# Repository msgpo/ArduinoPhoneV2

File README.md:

# ArduinoPhoneV2
Arduino Phone V2.0

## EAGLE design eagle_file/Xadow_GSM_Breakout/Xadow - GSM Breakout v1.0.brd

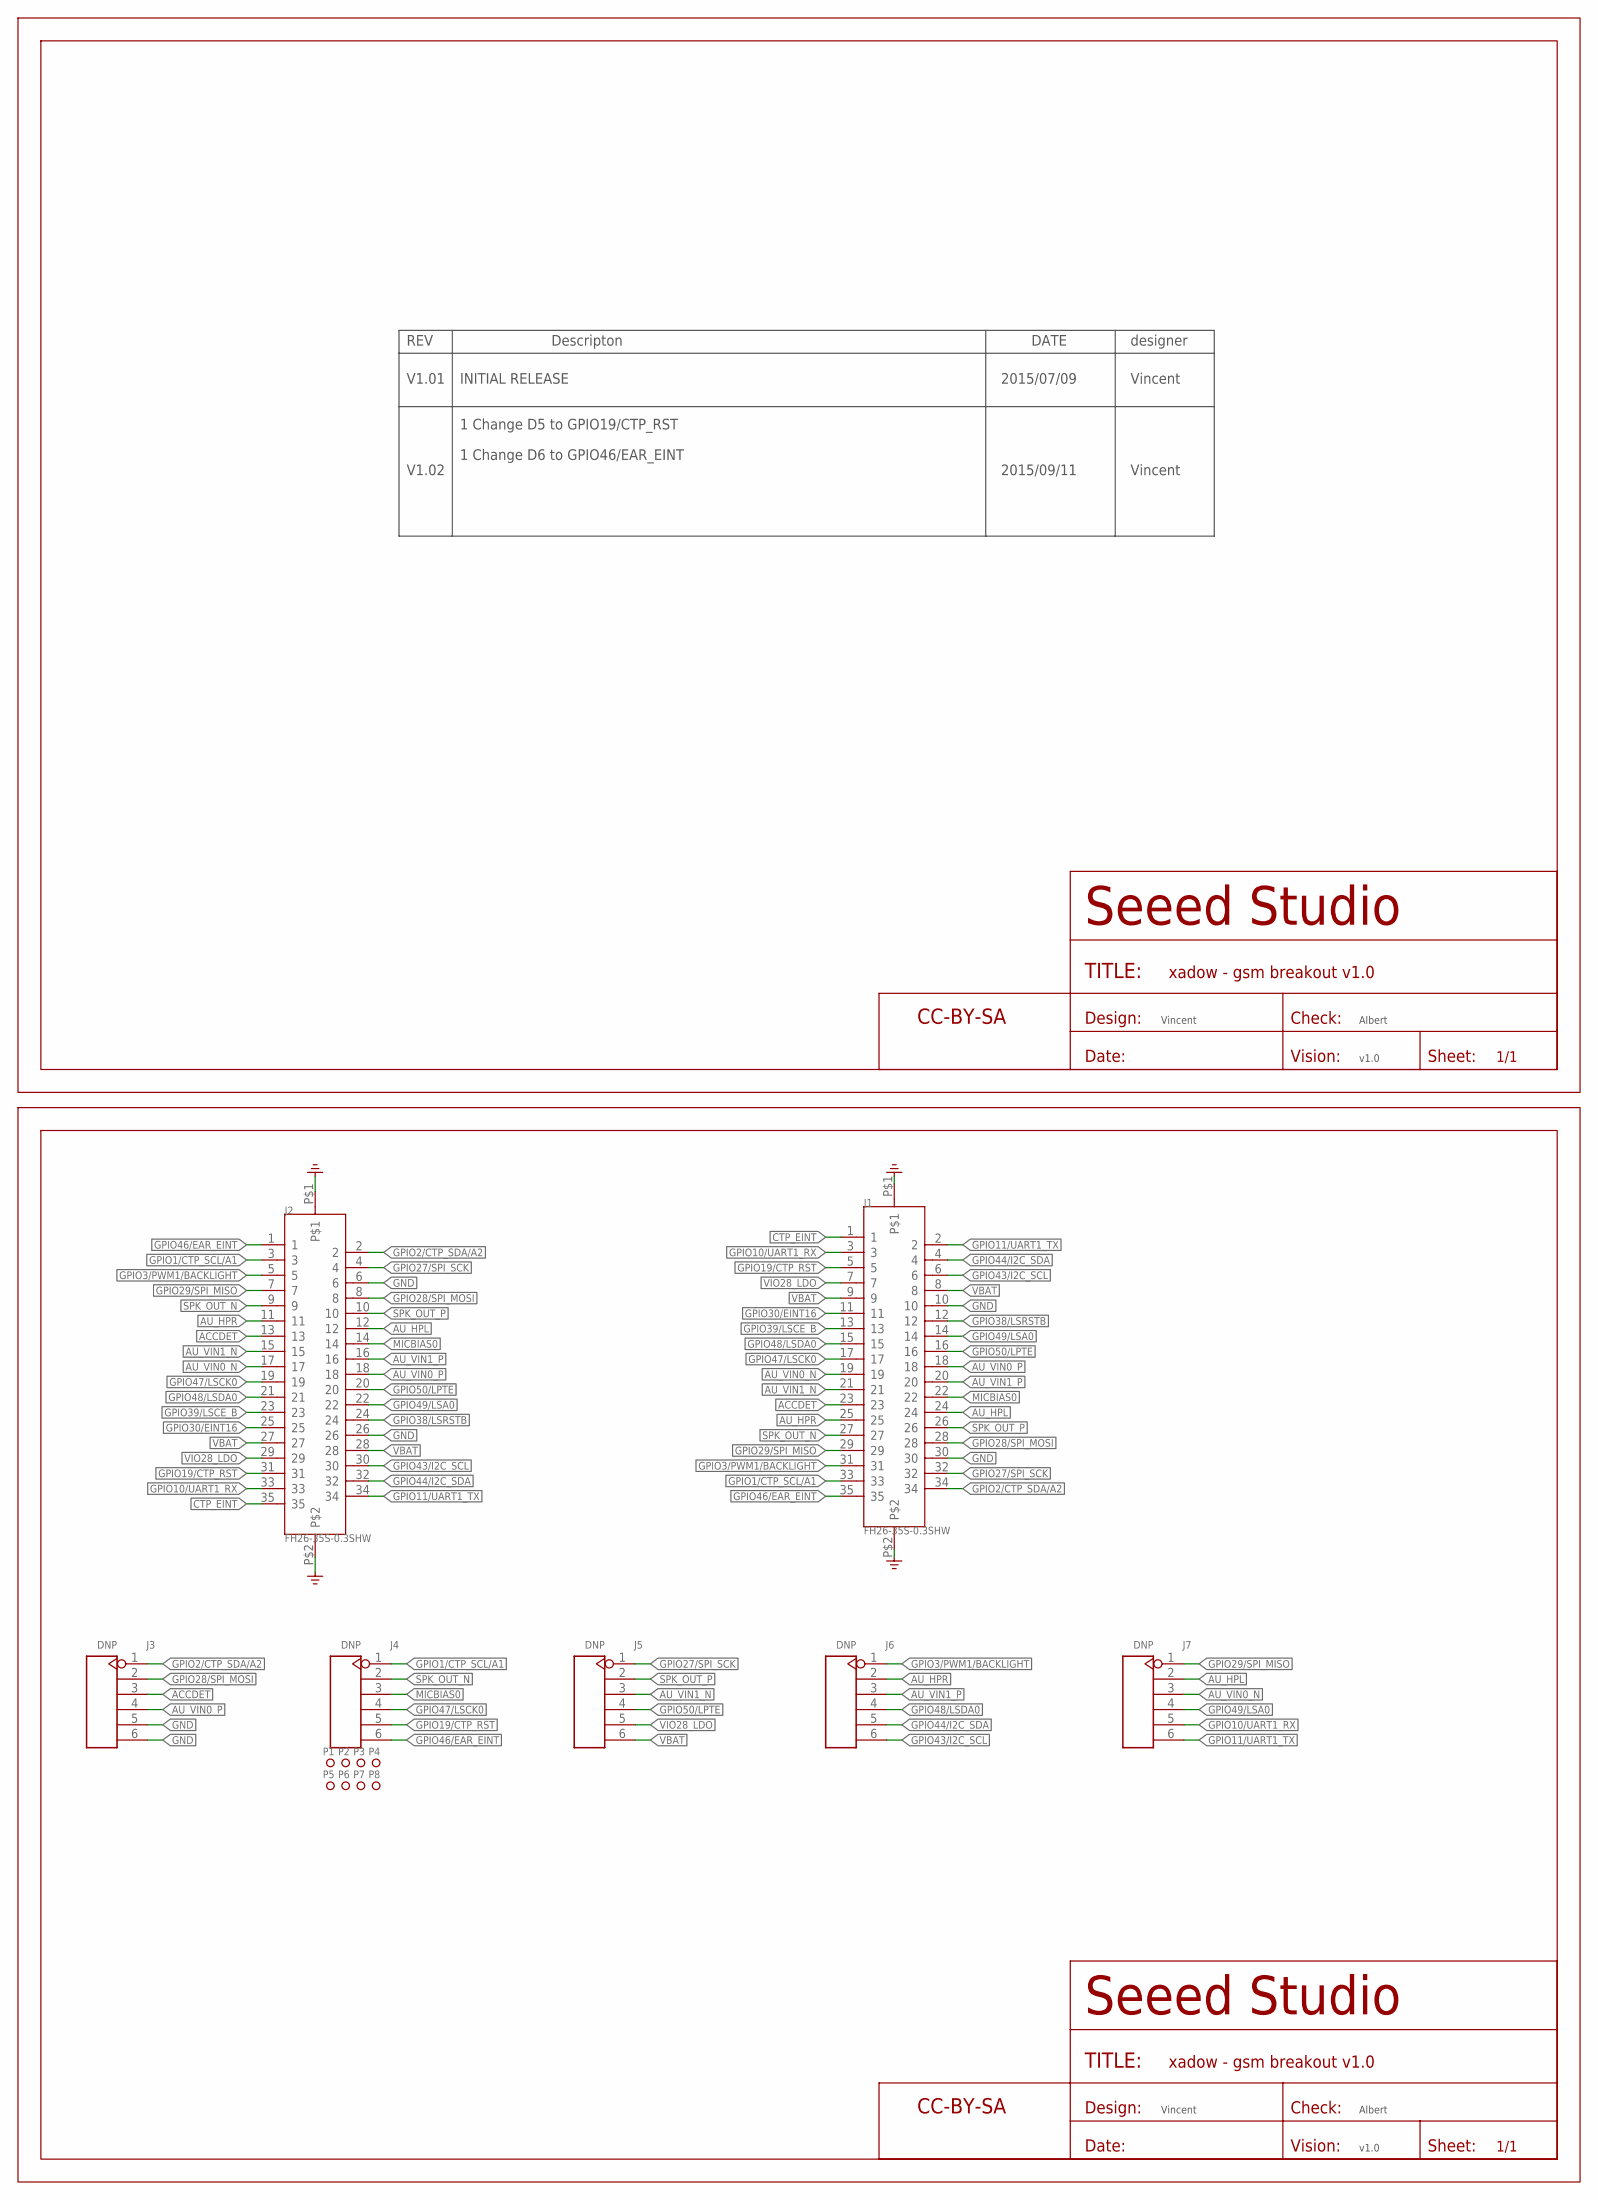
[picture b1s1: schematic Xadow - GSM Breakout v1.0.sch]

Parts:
FR1, FR2: SEEEDSTUDIO-OPEN-SCH-FRAME; SEEEDSTUDIO-PCB-FRAME
J1, J2: FH26-35S-0.3SHW; FPC35-SMD-0.3(FH26W)
J3, J4, J5, J6, J7: DNP; H6-2.54-C65D35MIL
P1, P2, P3, P4, P5, P6, P7, P8: MARK-1.0'ANNULAR'; ROUND-MARK-1.0

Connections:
ACCDET: J1.23, J2.13, J3.3
AU_HPL: J1.24, J2.12, J7.2
AU_HPR: J1.25, J2.11, J6.2
AU_VIN0_N: J1.19, J2.17, J7.3
AU_VIN0_P: J1.18, J2.18, J3.4
AU_VIN1_N: J1.21, J2.15, J5.3
AU_VIN1_P: J1.20, J2.16, J6.3
CTP_EINT: J1.1, J2.35
GND: J1.10, J1.30, J1.P$1, J1.P$2, J2.6, J2.26, J2.P$1, J2.P$2, J3.5, J3.6
GPIO1/CTP_SCL/A1: J1.33, J2.3, J4.1
GPIO2/CTP_SDA/A2: J1.34, J2.2, J3.1
GPIO3/PWM1/BACKLIGHT: J1.31, J2.5, J6.1
GPIO10/UART1_RX: J1.3, J2.33, J7.5
GPIO11/UART1_TX: J1.2, J2.34, J7.6
GPIO19/CTP_RST: J1.5, J2.31, J4.5
GPIO27/SPI_SCK: J1.32, J2.4, J5.1
GPIO28/SPI_MOSI: J1.28, J2.8, J3.2
GPIO29/SPI_MISO: J1.29, J2.7, J7.1
GPIO30/EINT16: J1.11, J2.25
GPIO38/LSRSTB: J1.12, J2.24
GPIO39/LSCE_B: J1.13, J2.23
GPIO43/I2C_SCL: J1.6, J2.30, J6.6
GPIO44/I2C_SDA: J1.4, J2.32, J6.5
GPIO46/EAR_EINT: J1.35, J2.1, J4.6
GPIO47/LSCK0: J1.17, J2.19, J4.4
GPIO48/LSDA0: J1.15, J2.21, J6.4
GPIO49/LSA0: J1.14, J2.22, J7.4
GPIO50/LPTE: J1.16, J2.20, J5.4
MICBIAS0: J1.22, J2.14, J4.3
SPK_OUT_N: J1.27, J2.9, J4.2
SPK_OUT_P: J1.26, J2.10, J5.2
VBAT: J1.8, J1.9, J2.27, J2.28, J5.6
VIO28_LDO: J1.7, J2.29, J5.5

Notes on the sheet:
REV
Descripton
DATE
designer
V1.01
INITIAL RELEASE
V1.02
1 Change D5 to GPIO19/CTP_RST
2015/07/09
2015/09/11
Vincent
1 Change D6 to GPIO46/EAR_EINT
Albert
v1.0

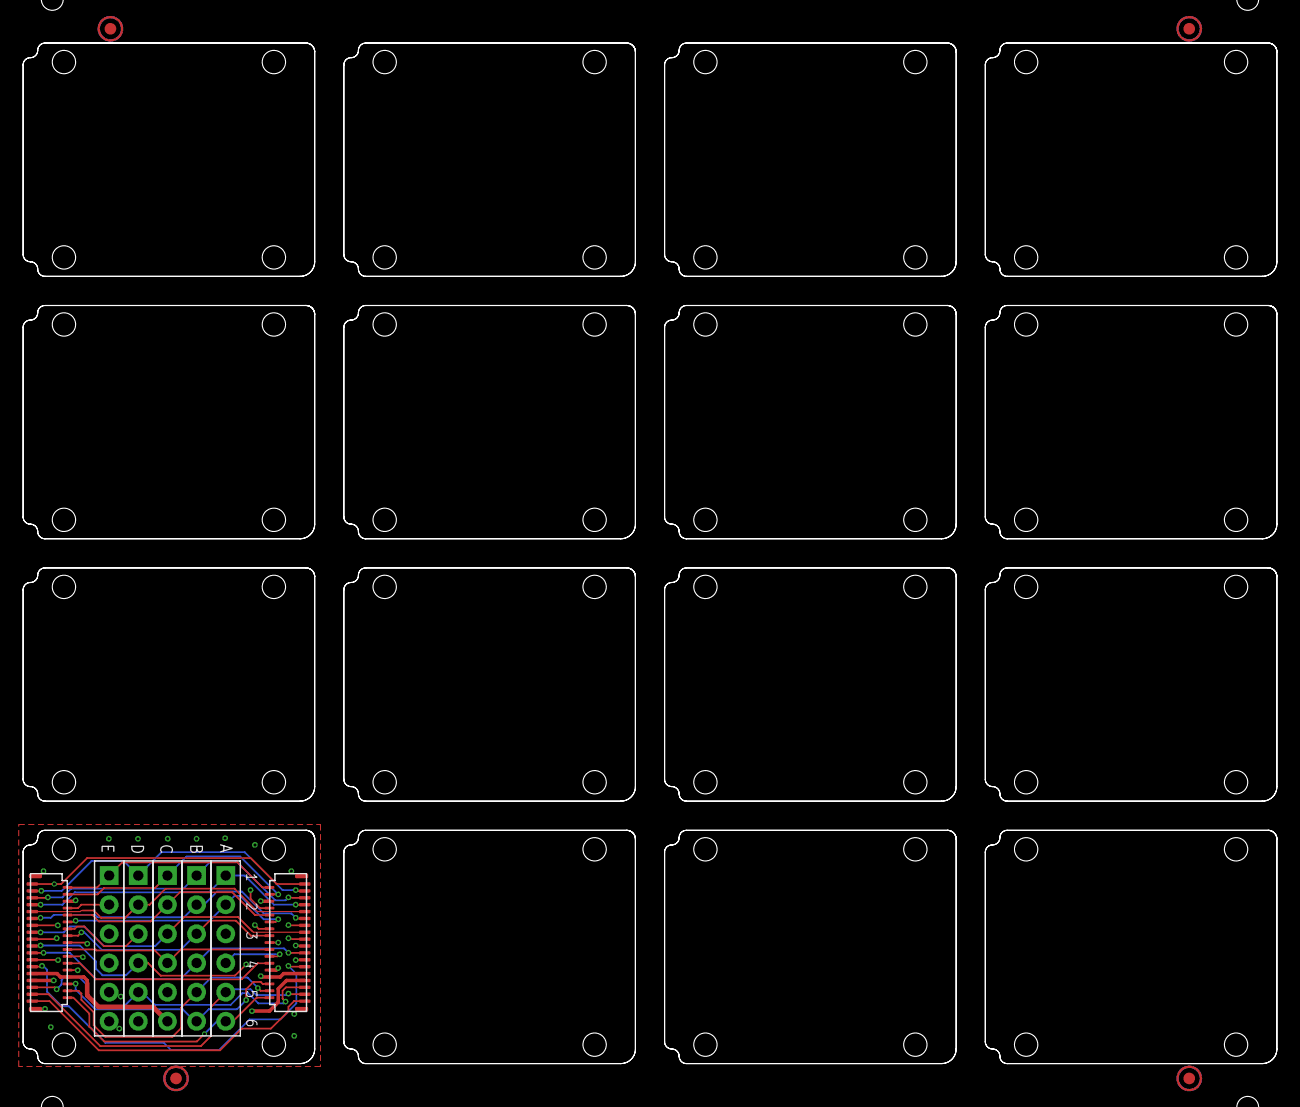
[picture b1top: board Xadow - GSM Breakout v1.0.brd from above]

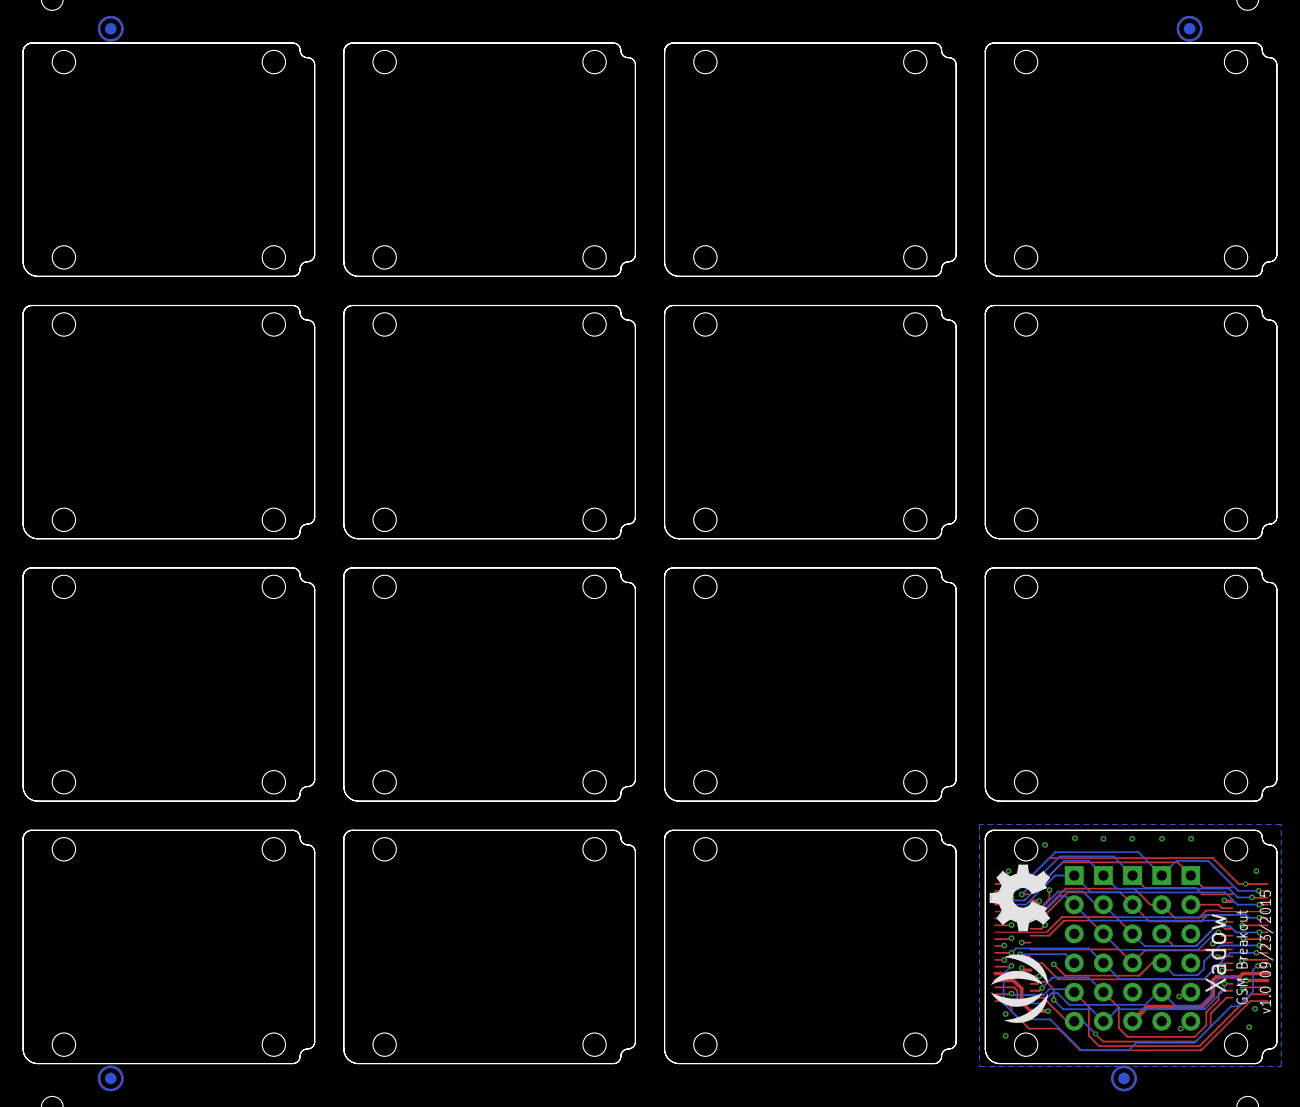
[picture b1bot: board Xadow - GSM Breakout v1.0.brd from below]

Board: 4 copper layers, 109.2 x 88.9 mm, 19 parts (6 on the bottom side), 33 nets.

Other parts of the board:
U$18: OSHW_FILLX200_NOTEXT
U$20: SEEED-SILK-280*268MIL

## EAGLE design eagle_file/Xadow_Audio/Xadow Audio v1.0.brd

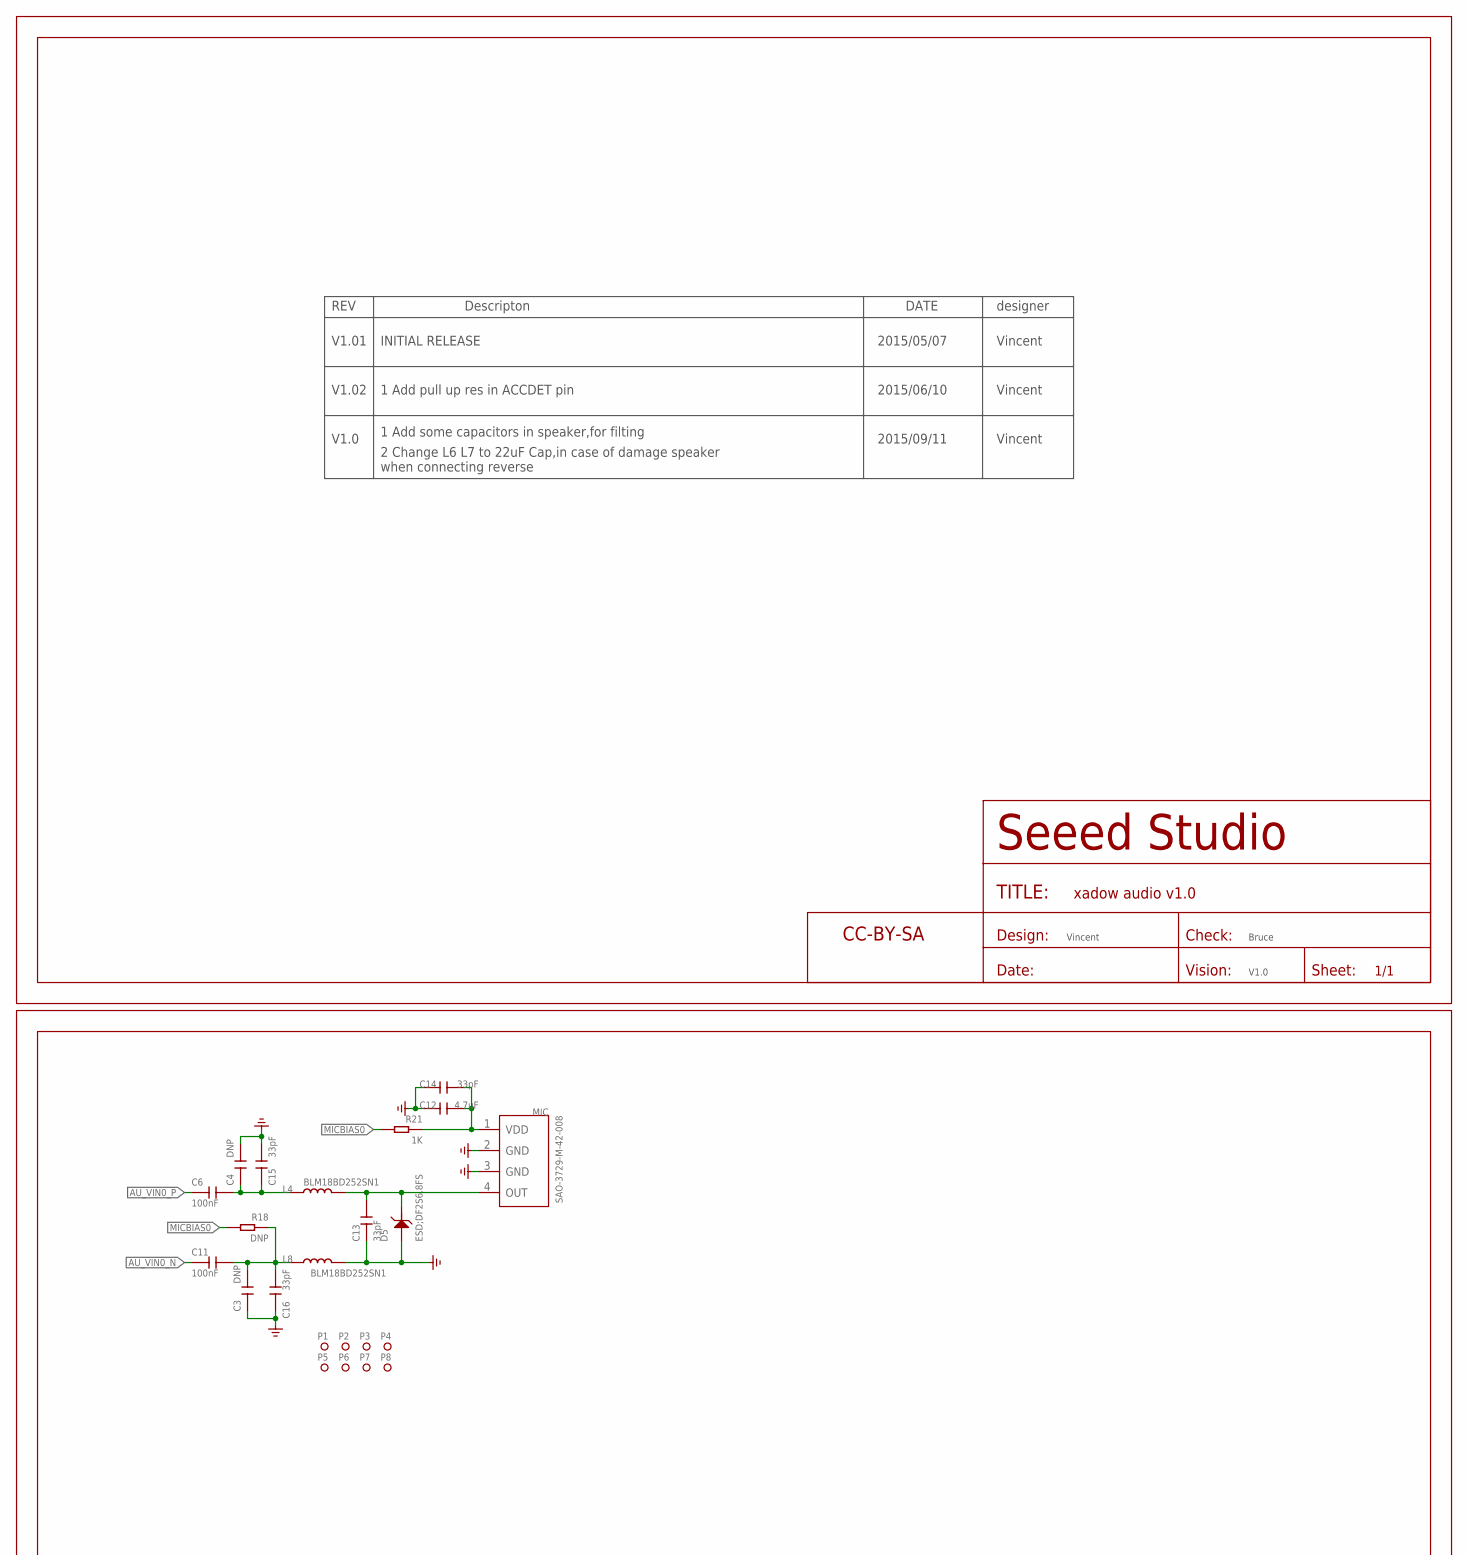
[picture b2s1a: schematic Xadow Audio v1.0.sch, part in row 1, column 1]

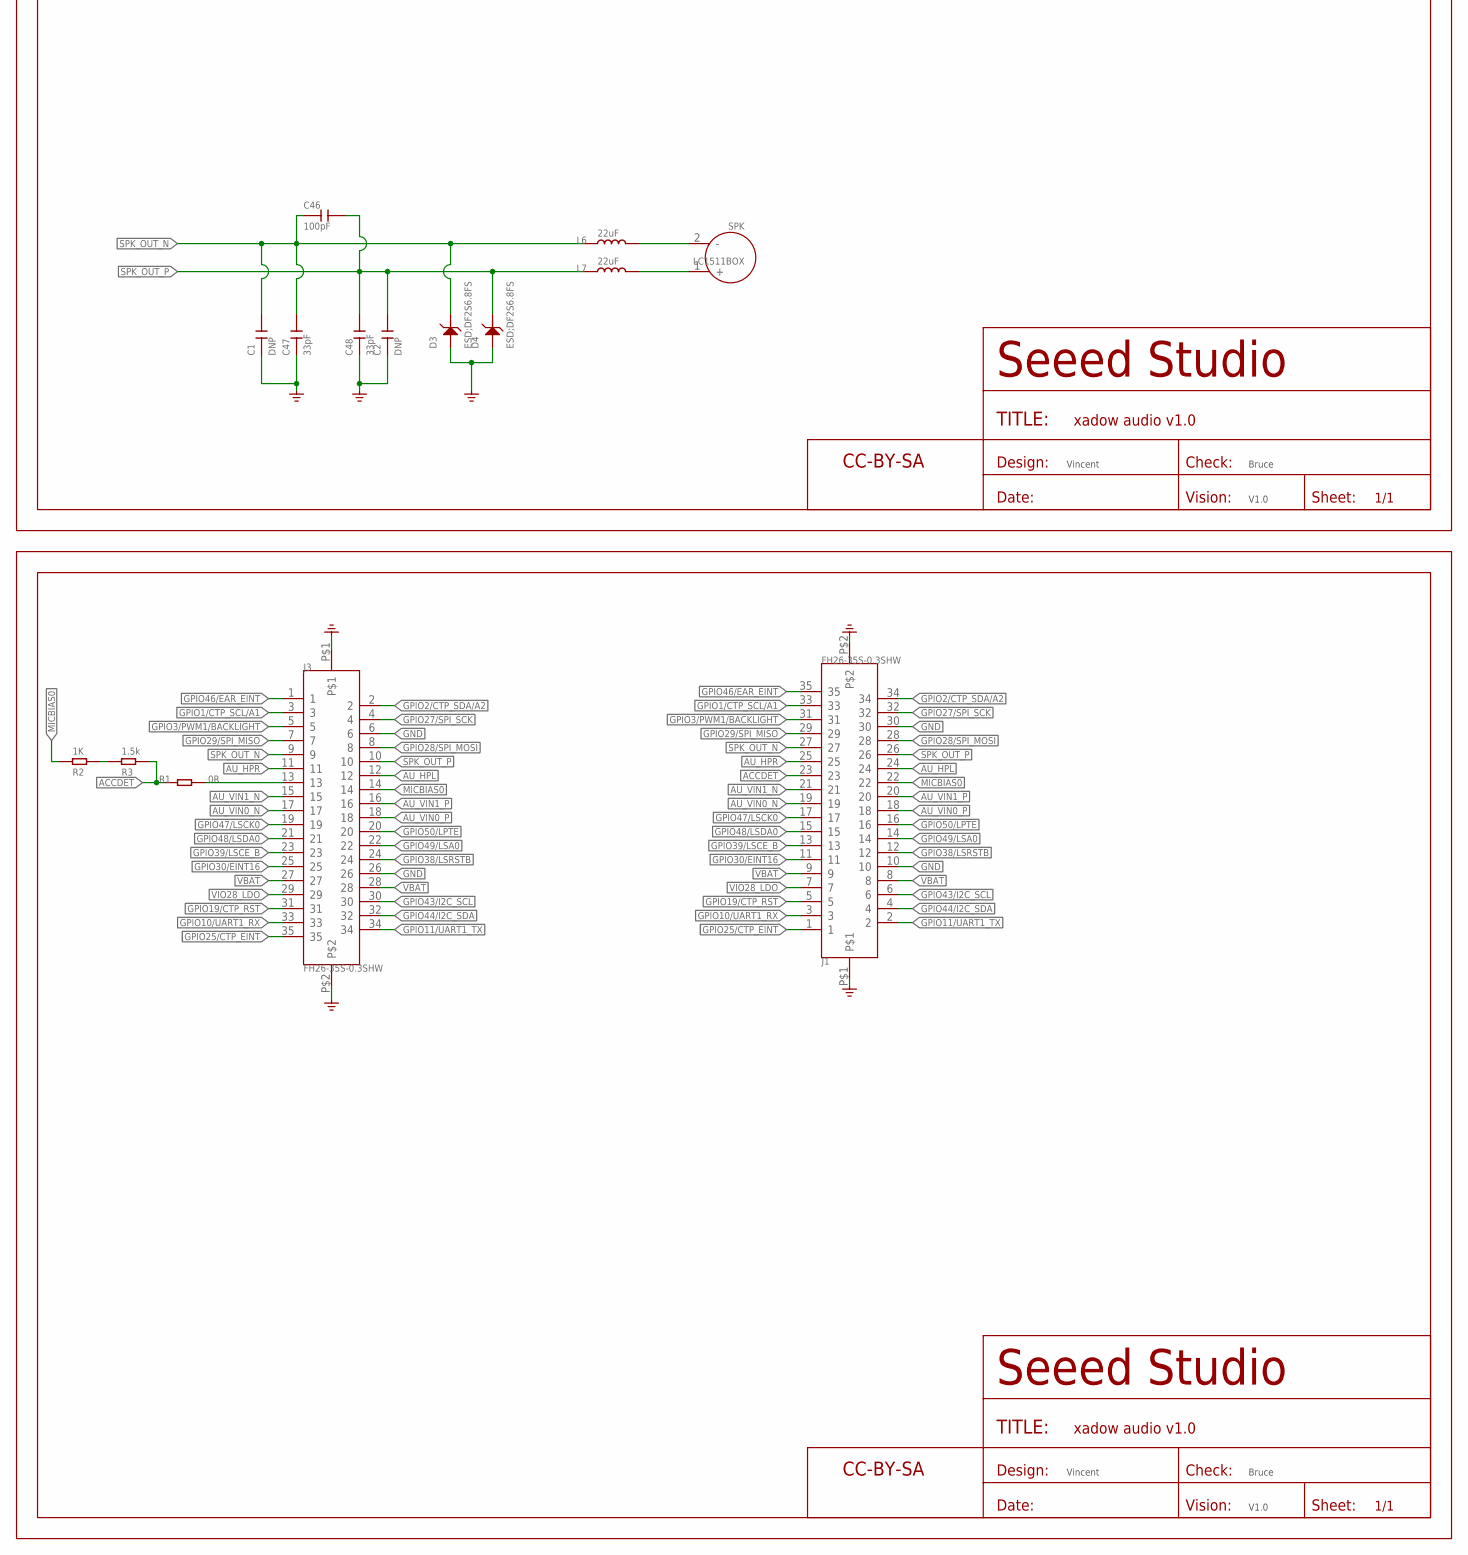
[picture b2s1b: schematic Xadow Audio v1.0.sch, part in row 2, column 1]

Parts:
C1, C2, C3, C4: DNP; C0402
C6, C11: 100nF; C0402
C12: 4.7uF; C0402
C13, C14, C15, C16, C47, C48: 33pF; C0402
C46: 100pF; C0402
D3, D4, D5: ESD;DF2S6.8FS; SOD-923
FR1: SEEEDSTUDIO-OPEN-SCH-FRAME; SEEEDSTUDIO-PCB-FRAME
J1, J3: FH26-35S-0.3SHW; FPC35-SMD-0.3(FH26W)
L4, L8: BLM18BD252SN1; L0603
L6, L7: 22uF; L0603
MIC: SAO-3729-M-42-008; MIC4-SMD-3.76X2.95MM
P1, P2, P3, P4, P5, P6, P7, P8: MARK-1.0'ANNULAR'; ROUND-MARK-1.0
R1: 0R; R0402
R2, R21: 1K; R0402
R3: 1.5k; R0402
R18: DNP; R0402
SPK: LC1511BOX; 2P-SMD-SPEAKER
U$1, U$2: SEEEDSTUDIO-OPEN-SCH-FRAME; SEEEDSTUDIO-PCB-FRAME

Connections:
ACCDET: J1.23, R1.2, R3.2
AU_HPL: J1.24, J3.12
AU_HPR: J1.25, J3.11
AU_VIN0_N: C11.1, J1.19, J3.17
AU_VIN0_P: C6.1, J1.18, J3.18
AU_VIN1_N: J1.21, J3.15
AU_VIN1_P: J1.20, J3.16
GND: C1.1, C2.1, C3.1, C4.2, C12.2, C13.1, C14.2, C15.2, C16.1, C47.1, C48.1, D3.2 (1), D4.2 (1), D5.2 (1), J1.10, J1.30, J1.P$1, J1.P$2, J3.6, J3.26, J3.P$1, J3.P$2, L8.2, MIC.2 (GND), MIC.3 (GND)
GPIO1/CTP_SCL/A1: J1.33, J3.3
GPIO2/CTP_SDA/A2: J1.34, J3.2
GPIO3/PWM1/BACKLIGHT: J1.31, J3.5
GPIO10/UART1_RX: J1.3, J3.33
GPIO11/UART1_TX: J1.2, J3.34
GPIO19/CTP_RST: J1.5, J3.31
GPIO25/CTP_EINT: J1.1, J3.35
GPIO27/SPI_SCK: J1.32, J3.4
GPIO28/SPI_MOSI: J1.28, J3.8
GPIO29/SPI_MISO: J1.29, J3.7
GPIO30/EINT16: J1.11, J3.25
GPIO38/LSRSTB: J1.12, J3.24
GPIO39/LSCE_B: J1.13, J3.23
GPIO43/I2C_SCL: J1.6, J3.30
GPIO44/I2C_SDA: J1.4, J3.32
GPIO46/EAR_EINT: J1.35, J3.1
GPIO47/LSCK0: J1.17, J3.19
GPIO48/LSDA0: J1.15, J3.21
GPIO49/LSA0: J1.14, J3.22
GPIO50/LPTE: J1.16, J3.20
MICBIAS0: J1.22, J3.14, R2.1, R18.2, R21.2
unnamed: J3.13, R1.1
unnamed: R2.2, R3.1
unnamed: C4.1, C6.2, C15.1, L4.1
unnamed: C3.2, C11.2, C16.2, L8.1, R18.1
unnamed: C12.1, C14.1, MIC.1 (VDD), R21.1
unnamed: C13.2, D5.1 (2), L4.2, MIC.4 (OUT)
unnamed: L6.2, SPK.2 (-)
unnamed: L7.2, SPK.1 (+)
SPK_OUT_N: C1.2, C46.1, C47.2, D3.1 (2), J1.27, J3.9, L6.1
SPK_OUT_P: C2.2, C46.2, C48.2, D4.1 (2), J1.26, J3.10, L7.1
VBAT: J1.8, J1.9, J3.27, J3.28
VIO28_LDO: J1.7, J3.29

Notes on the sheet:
Vincent
Bruce
V1.0
REV
Descripton
DATE
designer
V1.01
INITIAL RELEASE
V1.02
1 Add pull up res in ACCDET pin
2015/05/07
2015/06/10
1 Add some capacitors in speaker,for filting
2015/09/11
2 Change L6 L7 to 22uF Cap,in case of damage speaker when connecting reverse

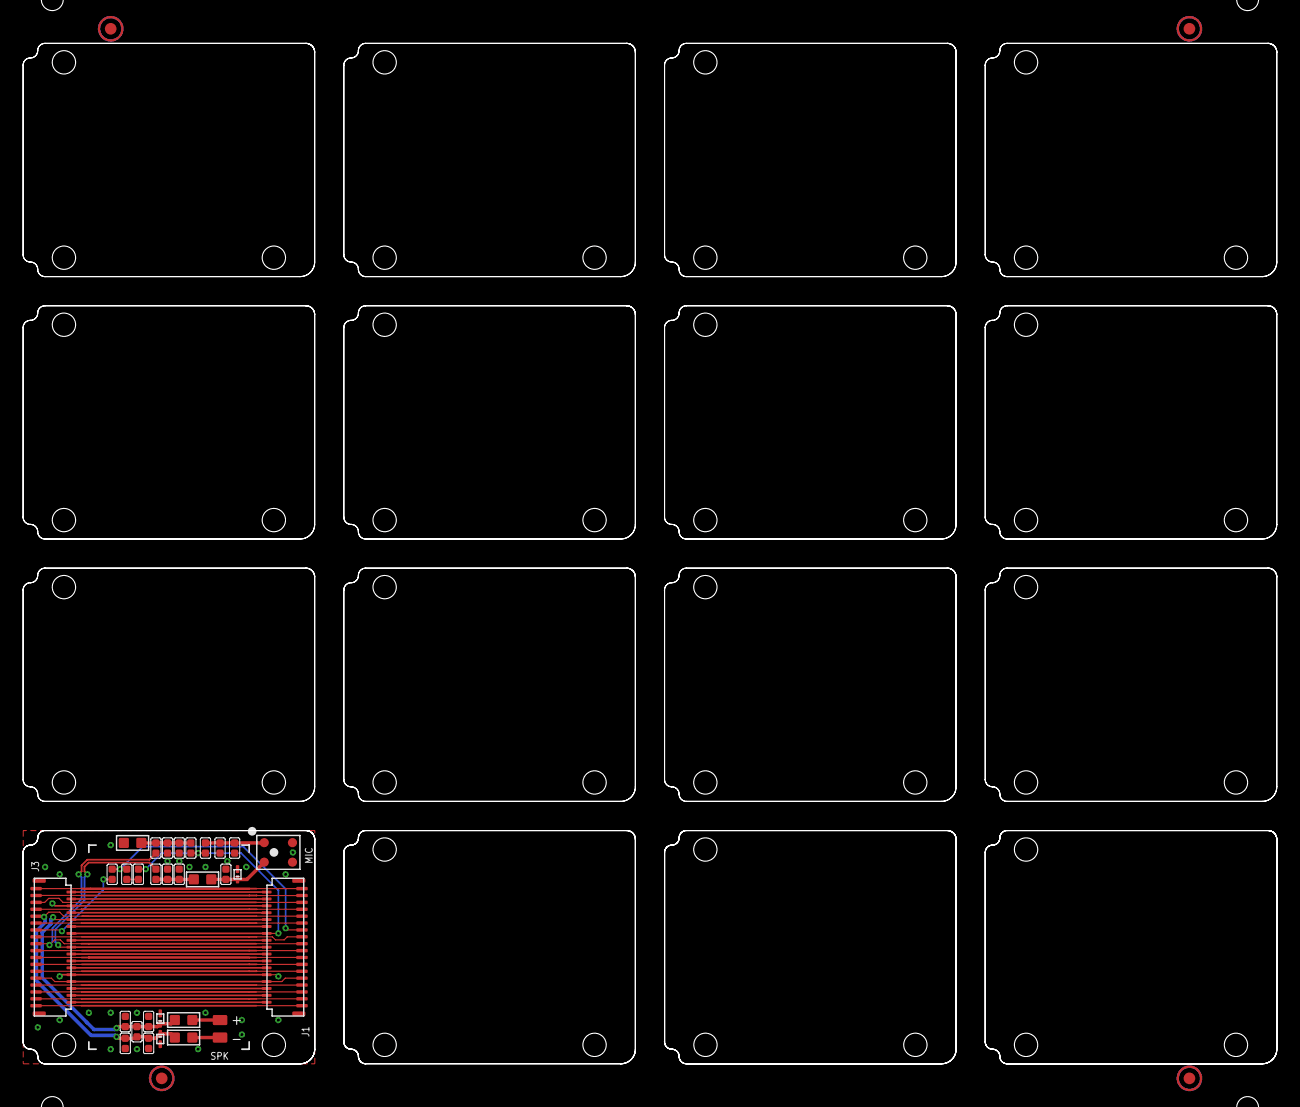
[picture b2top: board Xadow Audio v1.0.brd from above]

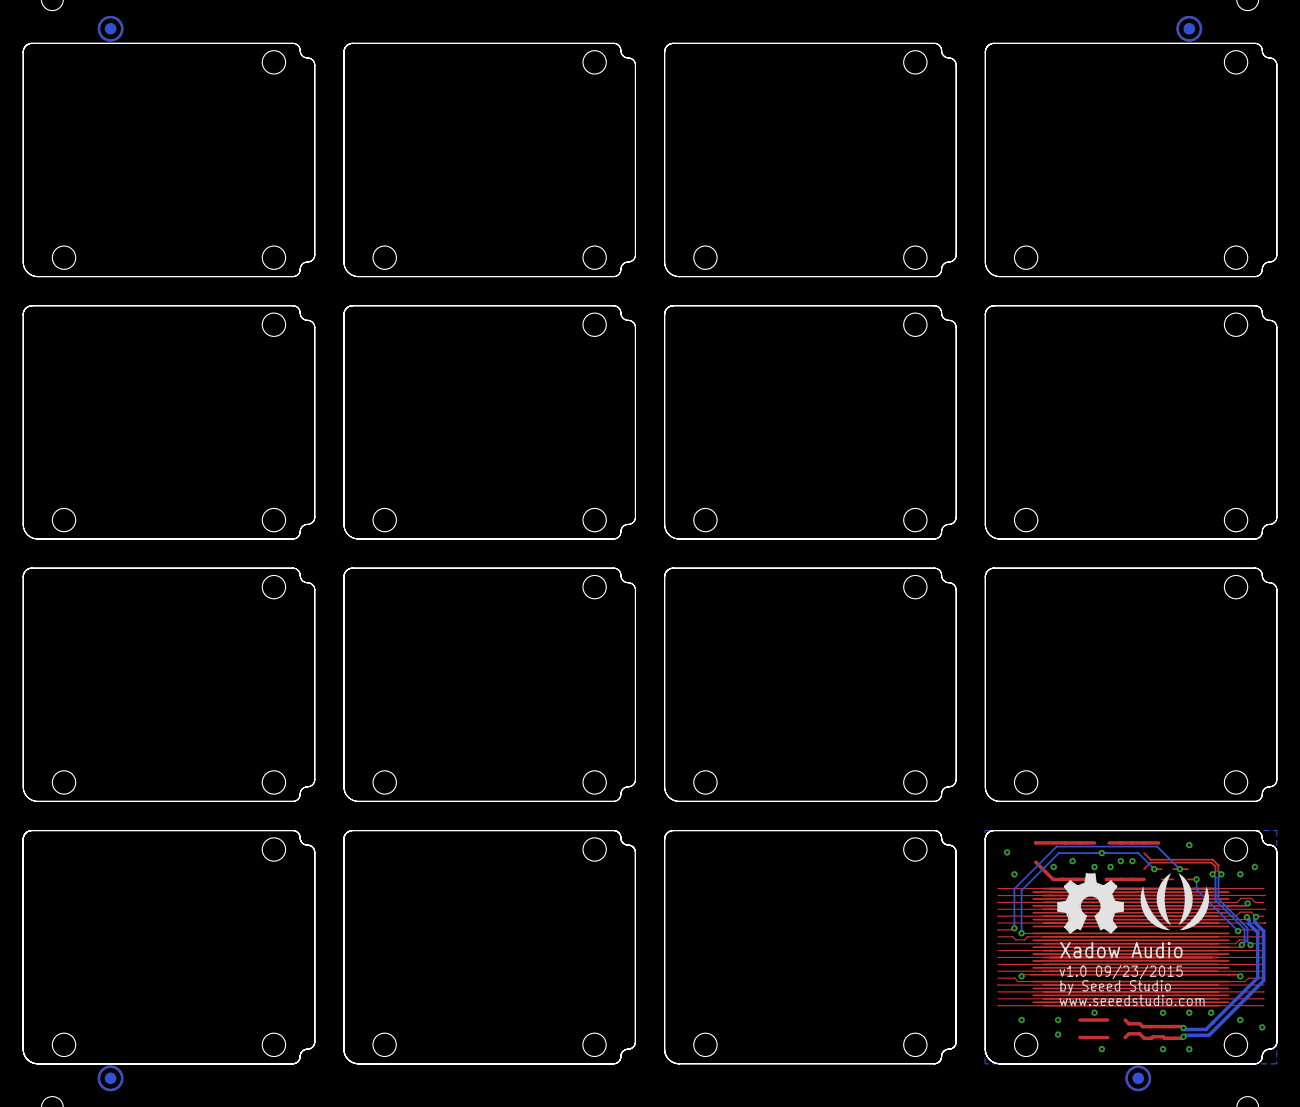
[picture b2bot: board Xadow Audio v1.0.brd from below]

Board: 2 copper layers, 109.2 x 88.9 mm, 43 parts (6 on the bottom side), 41 nets.

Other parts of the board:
U$3: OSHW_FILLX200_NOTEXT
U$4: SEEED-SILK-280*268MIL

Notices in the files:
parts and their libraries:
moudle-new: This work is licensed under the Creative Commons Attribution 4.0 International License.
To view a copy of this license,visit:
http://creativecommons.org/licenses/by-sa/4.0
moudle-new: CC-BY-SA
